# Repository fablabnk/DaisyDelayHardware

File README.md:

This repo documents the hardware design of a Daisy Seed-based Eurorack module called the Daisy Delay and contains the KiCad files for the project.

The Daisy Delay is planned as simple 6HP mono delay-line module, but can easily be used as a development platform for any kind of single-in/single-out audio processor.

This README gives an overview of the project, but there are also seperate notes for the [schematic](notes_schematic.md) and the [PCB](notes_pcb.md).

The module was first prototyped in VCVRack, before before being converted back to code that will run on the Seed. For more details on the VCVRack plugin, see [here](https://github.com/fablabnk/VaseProtoPlugin/tree/delay_line_params).

# Components / Bill of Materials (BOM)

The 

- 2 x 10K (for now) potentiometers
- 1 x SPST mini switch
- 1 x small LED (? diameter)
- 4 x Thonkiconn mono switching jack sockets (PJ301M-12)
- 1 x TL072 op amp
- 1 x TL074 op amp
- 1 x Shrouded 10 pin power connector
- various resistors
- various ceramic capacitors

# Workflow

Below is the basic workflow I am following to develop the module. 

1. Design schematic
- symbol and footprint for Seed Rev4 are already included in KiCad - search for "electrosmith"

2. Design front panel in Kicad PCB editor
- use VCV plugin panel .svg as template
- laser cut on paper / thin card first to test fit

3. Layout and Route PCB
- one board which drops onto components
- laser cut on paper / thin card first to test fit
- 2 layer / 4 layer routing?

4. Convert code to seed format
- test code on Pod

5. Send for fabrication (PCBWay)
- Order 5 x front and back panels

# Useful Links

https://github.com/clacktronics/Eurorack_KiCAD_templates

# Concerns / To Do

- Simpler hardware module first...probably!
- Symbol is only for Seed Rev 4 and we are now on Rev 7, but each Daisy Seed is pin to pin compatible with one another 
- Revisions were only to replace depricated audio codecs. See here: https://daisy.nyc3.cdn.digitaloceanspaces.com/products/seed/Daisy_Seed_datasheet.pdf

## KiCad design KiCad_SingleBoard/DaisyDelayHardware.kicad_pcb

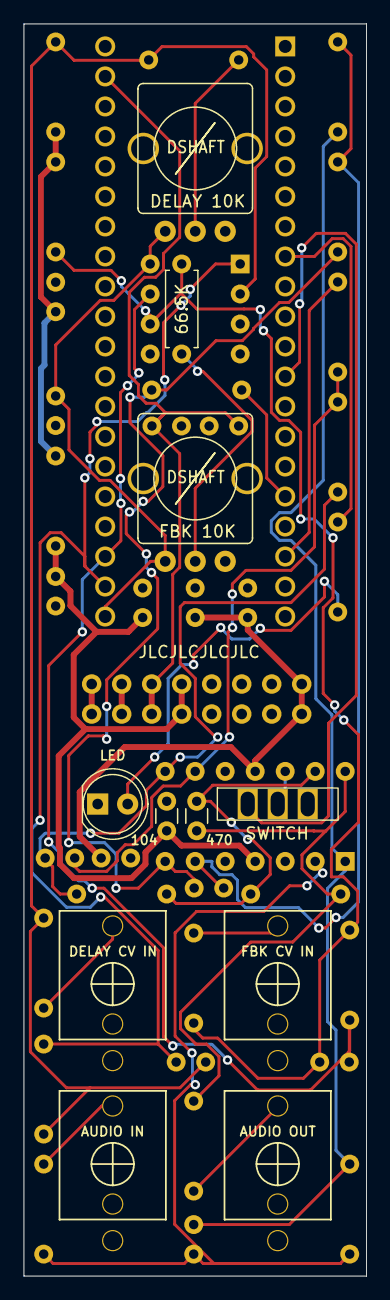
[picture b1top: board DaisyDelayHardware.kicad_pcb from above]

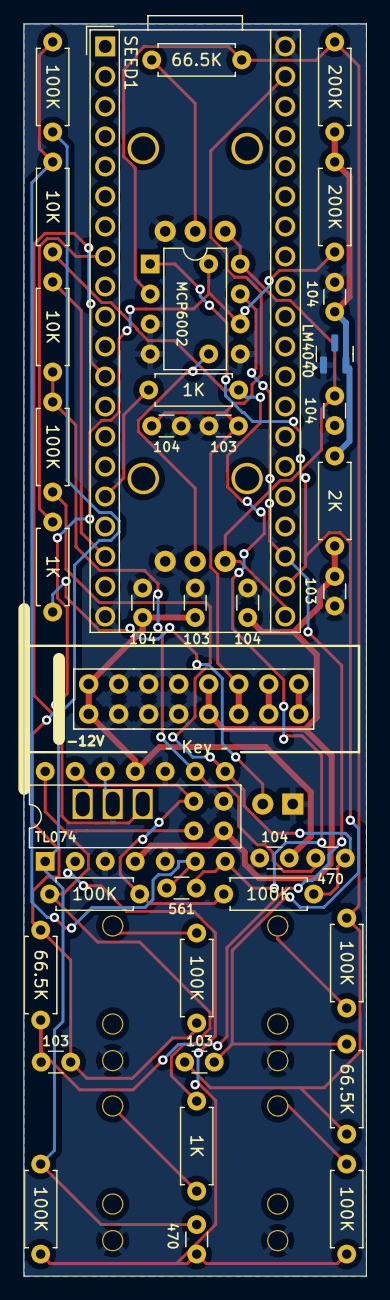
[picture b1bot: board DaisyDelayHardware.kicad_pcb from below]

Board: 2 copper layers, 29.0 x 106.0 mm, 49 parts (38 on the bottom side), 31 nets.

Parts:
C1, C6, C11, C12, C15: 103; C_Disc_D3.0mm_W1.6mm_P2.50mm
C2, C4, C5: 470; C_Disc_D3.0mm_W1.6mm_P2.50mm
C3: 561; C_Disc_D3.0mm_W1.6mm_P2.50mm
C7, C8, C9, C10, C13, C14, C16: 104; C_Disc_D3.0mm_W1.6mm_P2.50mm
D1: LED; LED_D5.0mm
J1: AUDIO OUT; PJ301M-12_T_S
J2: FBK CV IN; PJ301M-12_T_S
J3: DELAY CV IN; PJ301M-12_T_S
J5: AUDIO IN; PJ301M-12_T_S
J6: Eurorack_Power_16pin_Shrouded; Pins_2x08_2.54mm_TH_EuroPower_Shrouded
R1, R15: 200K; R_Axial_DIN0207_L6.3mm_D2.5mm_P7.62mm_Horizontal
R2, R5, R6, R8, R11, R12, R13, R16: 100K; R_Axial_DIN0207_L6.3mm_D2.5mm_P7.62mm_Horizontal
R3, R4, R17, R18: 66.5K; R_Axial_DIN0207_L6.3mm_D2.5mm_P7.62mm_Horizontal
R7, R14, R20: 1K; R_Axial_DIN0207_L6.3mm_D2.5mm_P7.62mm_Horizontal
R9, R10: 10K; R_Axial_DIN0207_L6.3mm_D2.5mm_P7.62mm_Horizontal
R19: 2K; R_Axial_DIN0207_L6.3mm_D2.5mm_P7.62mm_Horizontal
RV1: DELAY 10K; Pot_9mm_DShaft
RV2: FBK 10K; Pot_9mm_DShaft
SEED1: Electrosmith_Daisy_Seed_Rev4; Electrosmith_Daisy_Seed
SWITCH: SW_SPDT; SW_Slide-03_Wuerth-WS-SLTV_10x2.5x6.4_P2.54mm-SolderLugs
U1: LM4040; SOT-23
U2: TL074; DIP-14_W7.62mm
U3: MCP6002; DIP-8_W7.62mm

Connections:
+3V3: C8.1, RV1.1, RV2.1, SEED1.21 (3V3_A), U3.8 (V+)
+5V: C15.1, C16.1, J6.5 (+12V), J6.6, SEED1.39 (VIN)
+12V: C10.1, C12.2, C13.2, J6.7 (12V), J6.8 (+12V), R19.1, U2.4 (V+)
-10V: C7.1, R1.1, R15.1, R19.2, U1.2 (A)
-12V: C9.2, C11.1, C14.1, J6.15 (-12V), J6.16, U2.11 (V-)
ADC_IN_0: C1.2, R4.2, SEED1.22 (ADC_0), U3.1
ADC_IN_1: C6.2, R18.2, SEED1.23 (ADC_1), U3.7
AUDIO_IN_L: R7.2, SEED1.16 (AUDIO_IN_1)
AUDIO_OUT_L: R10.1, SEED1.18 (AUDIO_OUT_1)
GND: C7.2, C8.2, C9.1, C10.2, C11.2, C12.1, C13.1, C14.2, C15.2, C16.2, D1.1 (K), J1.S, J2.S, J3.S, J5.S, J6.9 (GND), J6.10 (GND), J6.11 (GND), J6.12 (GND), J6.13 (-12), J6.14 (-12V), RV1.3, RV2.3, SEED1.20 (AGND), SEED1.40 (DGND), SWITCH.1 (A), U1.1 (K), U2.3 (+), U2.5 (+), U2.10 (+), U2.12 (+), U3.3 (+), U3.4 (V-), U3.5 (+)
LED_OUT: R20.1, SEED1.8 (SPI1_CS)
unnamed: C2.2, R6.1, R8.2, U2.1
unnamed: C3.2, R7.1, R9.2, U2.7
unnamed: C4.2, R11.2, R12.1, U2.8
unnamed: C5.2, R13.2, R14.1, U2.14
unnamed: D1.2 (A), R20.2
unnamed: J1.T, R14.2
unnamed: J2.T, R16.1
unnamed: J3.T, R2.1
unnamed: J5.T, R5.1
unnamed: J6.1, J6.2
unnamed: J6.3, J6.4
unnamed: R3.1, RV1.2
unnamed: R17.1, RV2.2
unnamed: C2.1, R5.2, R8.1, U2.2 (-)
unnamed: C3.1, R6.2, R9.1, U2.6 (-)
unnamed: C4.1, R10.2, R11.1, U2.9 (-)
unnamed: C5.1, R12.2, R13.1, U2.13 (-)
unnamed: C1.1, R1.2, R2.2, R3.2, R4.1, U3.2 (-)
unnamed: C6.1, R15.2, R16.2, R17.2, R18.1, U3.6 (-)
SWITCH_IN: SEED1.12 (I2C1_SCL), SWITCH.2 (B)

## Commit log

2024-04-17 routed first pcb
2024-05-06 commiting before updating routing
2024-06-06 latest updates
2024-06-08 added single board version of project - half-routed
2024-06-13 backup before pcb revision
2024-06-15 pcb revised - but doesn't meet jlcpcb design rules
2024-06-15 DRC now adheres to custom design rules for jlcpcb
